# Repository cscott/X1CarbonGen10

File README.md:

# Input Module for Thinkpad X1 Carbon Gen 10 keyboard

This module is based on the "Microcontroller Input Module" example
from https://github.com/FrameworkComputer/InputModules which in turn
is based on the Adafruit Feather RP2040 (https://www.adafruit.com/product/4884).

More discussion of this project, and of replacement keyboards for
the Framework 16 laptop generally, can be found in the [Framework
forums](https://community.frame.work/t/thinkpad-keyboard-mod-super-early-stages/38484/58).

## License
Input Modules © 2023 by Framework Computer Inc is licensed under CC BY 4.0.

This module for the Thinkpad X1 Carbon Gen 10 keyboard is © 2024 by
C. Scott Ananian and is also licensed under CC BY 4.0.

To view a copy of this license,
visit http://creativecommons.org/licenses/by/4.0/

## Fabrication and Assembly
A 0.8mm PCB is recommended.

All components are SMT on the bottom side of the board.

To enter boot mode on the RP2040 to reflash, hold down the "Fn" key on
the keyboard as power is applied.

## BOM
You can find alternatives for just about each of these components
except for the microcontroller.  The keyboard FPC is designed to be inserted
with contacts facing down toward the PCB, which is "up" (since the connector
is on the bottom side of the board) and thus will require folding the
keyboard's FPC cable to achieve the proper orientation.

Notes: 1uF caps are 2.2uF in pico reference design and it had one more 100nF cap on 1v1;
match crystal caps to crystal selected.

| Item # | Designator                                         | Qty | Manufacturer                        | Mfg Part #               | Description / Value | Package/Footprint                                    | Type |
|--------|----------------------------------------------------|-----|-------------------------------------|--------------------------|---------------------|------------------------------------------------------|------|
| 1      | C1, C4, C6, C9, C11, C12, C13, C14, C15, C16, C17, C18, C20 | 13  | Samsung                    | CL05B104KO5NNNC          | 100nF               | Capacitor_SMD:C_0402_1005Metric                      | SMT  |
| 2      | C2, C3                                             | 2   | Murata                              | GRM1555C1H150JA01D       | 15pF                | Capacitor_SMD:C_0402_1005Metric                      | SMT  |
| 3      | C5, C8, C19, C21, C22, C23                         | 6   | TDK                                 | C1608X5R1A106M080AC      | 10uF                | Capacitor_SMD:C_0603_1608Metric                      | SMT  |
| 4      | C7, C10                                            | 2   | Samsung                             | CL05A105KO5NNNC          | 1uF                 | Capacitor_SMD:C_0402_1005Metric                      | SMT  |
| 5      | D1, D2, D3, D4, D5                                 | 5   | Littelfuse                          | SP0402B-ULC-01ETG        | D_TVS               | Diode_SMD:D_0402_1005Metric                          | SMT  |
| 6      | H1, H2                                             | 2   | Keystone                            | 24929                    | 24929               | InputModule:MountingHole_3.7mm_Pad_24929             | SMT  |
| 7      | J2                                                 | 1   | HDGC                                | 0.3K-HX-45PWB            | 45-pin FPC connector | 20655-045E-01:0.3K-HX-45PWB                         | SMT  |
| 8      | R1, R3                                             | 2   | Yageo                               | RC0402FR-071KL           | 1k                  | Resistor_SMD:R_0402_1005Metric                       | SMT  |
| 9      | R2                                                 | 1   | Yageo                               | RC0402FR-07330KL         | 330k                | Resistor_SMD:R_0402_1005Metric                       | SMT  |
| 10     | R4, R5                                             | 2   | Panasonic                           | ERJ-2RKF27R0X            | 27                  | Resistor_SMD:R_0402_1005Metric                       | SMT  |
| 11     | R6, R7, R8, R9                                     | 4   | Panasonic                           | ERJ-2RKF1000X            | 100                 | Resistor_SMD:R_0402_1005Metric                       | SMT  |
| 12     | U1                                                 | 1   | Winbond                             | W25Q16JVUXIQ             | W25Q16JVUXIQ        | InputModule:SON-8-1EP_3x2mm_P0.5mm_EP0.2x1.6mm       | SMT  |
| 13     | U2                                                 | 1   | Raspberry Pi                        | RP2040TR7                | RP2040              | Package_DFN_QFN:QFN-56-1EP_7x7mm_P0.4mm_EP3.2x3.2mm  | SMT  |
| 14     | U3                                                 | 1   | Microchip                           | MCP23S17_ML              | MCP23S17_ML         | Package_DFN_QFN:QFN-28-1EP_6x6mm_P0.65mm_EP4.25x4.25mm | SMT|
| 15     | Y1                                                 | 1   | Abracon                             | ABM8G-12.000MHZ-18-D2Y-T | 12.000MHz           | Crystal:Crystal_SMD_3225-4Pin_3.2x2.5mm              | SMT  |

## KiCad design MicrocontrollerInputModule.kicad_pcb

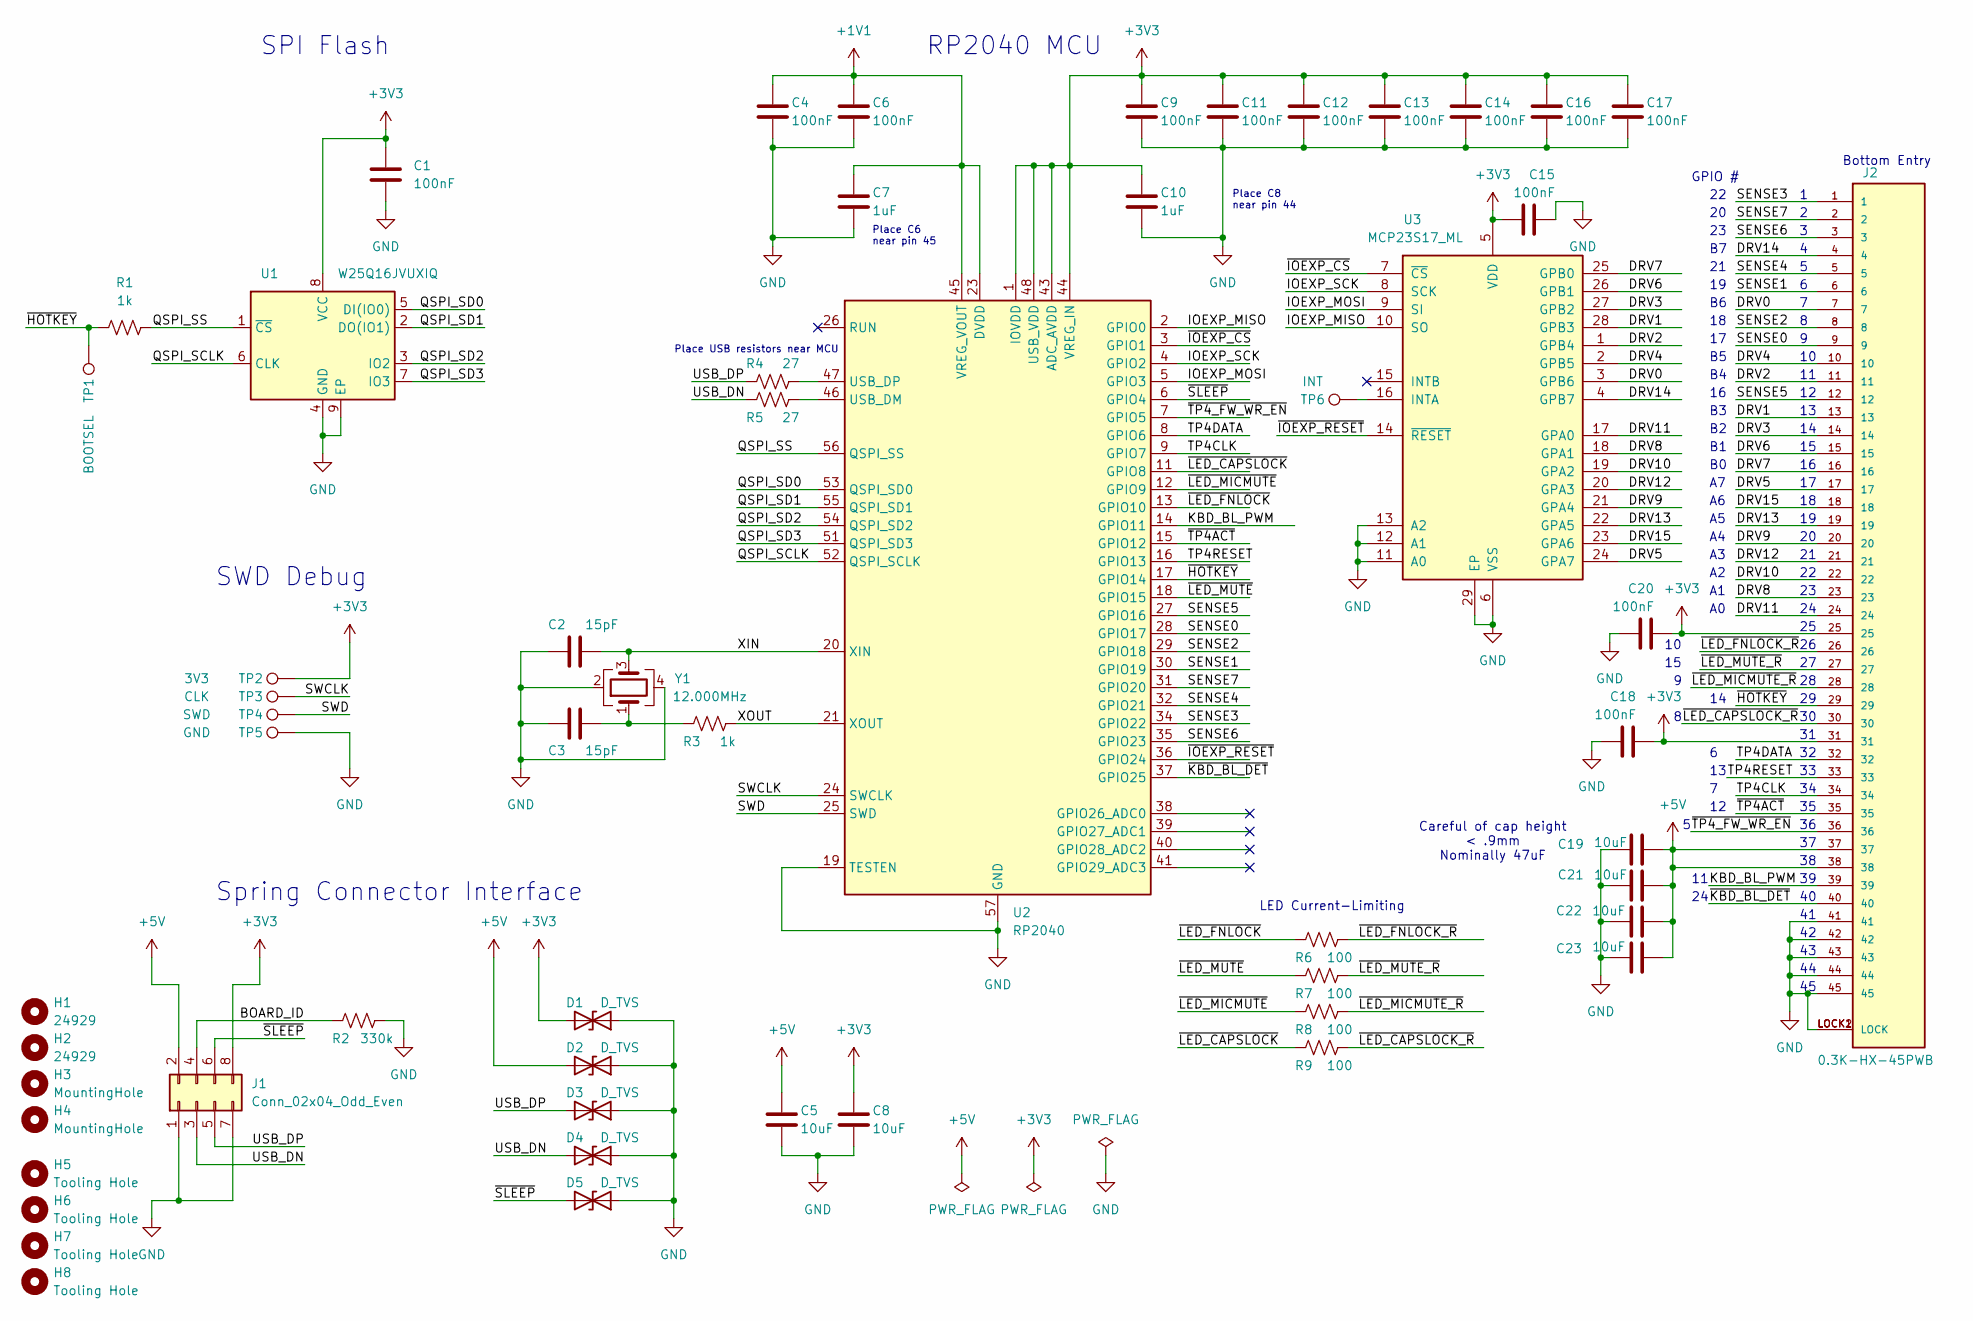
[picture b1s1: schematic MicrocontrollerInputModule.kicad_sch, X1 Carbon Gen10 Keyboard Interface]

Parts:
C1, C4, C6, C9, C11, C12, C13, C14, C15, C16, C17, C18, C20: 100nF; C_0402_1005Metric; LCSC C1525
C2, C3: 15pF; C_0402_1005Metric; LCSC C1555
C5, C8, C19, C21, C22, C23: 10uF; C_0603_1608Metric; LCSC C96446
C7, C10: 1uF; C_0402_1005Metric; LCSC C52923
D1, D2, D3, D4, D5: D_TVS; D_0402_1005Metric; LCSC C468904
H1, H2: 24929; MountingHole_3.7mm_Pad_24929; LCSC C5354888
H3, H4: MountingHole; MountingHole_2.1mm
H5, H6, H7, H8: Tooling Hole; JLCPCB Tooling Hole
J1: Conn_02x04_Odd_Even; PogoPads_2x4_P2.0mm
J2: 0.3K-HX-45PWB; PARTREV 5
R1, R3: 1k; R_0402_1005Metric; LCSC C11702
R2: 330k; R_0603_1608Metric; LCSC C23137
R4, R5: 27; R_0402_1005Metric; LCSC C138021
R6, R7, R8, R9: 100; R_0402_1005Metric; LCSC C25076
TP1: BOOTSEL; TestPoint_Pad_D1.0mm
TP2: 3V3; TestPoint_Pad_D1.0mm
TP3: CLK; TestPoint_Pad_D1.0mm
TP4: SWD; TestPoint_Pad_D1.0mm
TP5: GND; TestPoint_Pad_D1.0mm
TP6: INT; TestPoint_Pad_D1.0mm
U1: W25Q16JVUXIQ; SON-8-1EP_3x2mm_P0.5mm_EP0.2x1.6mm; LCSC C2843335
U2: RP2040; QFN-56-1EP_7x7mm_P0.4mm_EP3.2x3.2mm; LCSC C2040
U3: MCP23S17_ML; QFN-28-1EP_6x6mm_P0.65mm_EP4.25x4.25mm; LCSC C629442
Y1: 12.000MHz; Crystal_SMD_3225-4Pin_3.2x2.5mm; LCSC C9002

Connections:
+1V1: C4.1, C6.1, C7.1, U2.23 (DVDD), U2.45 (VREG_VOUT), U2.50 (DVDD)
+3V3: C1.1, C8.1, C9.1, C10.1, C11.1, C12.1, C13.1, C14.1, C15.1, C16.1, C17.1, C18.2, C20.2, D1.2 (A2), J1.8, J2.25, J2.31, TP2.1, U1.8 (VCC), U2.1 (IOVDD), U2.10 (IOVDD), U2.22 (IOVDD), U2.33 (IOVDD), U2.42 (IOVDD), U2.43 (ADC_AVDD), U2.44 (VREG_IN), U2.48 (USB_VDD), U2.49 (IOVDD), U3.5 (VDD)
+5V: C5.1, C19.2, C21.2, C22.2, C23.2, D2.2 (A2), J1.2, J2.37, J2.38
/BOARD_ID: J1.4, R2.1
/DRV0: J2.7, U3.3 (GPB6)
/DRV1: J2.13, U3.28 (GPB3)
/DRV2: J2.11, U3.1 (GPB4)
/DRV3: J2.14, U3.27 (GPB2)
/DRV4: J2.10, U3.2 (GPB5)
/DRV5: J2.17, U3.24 (GPA7)
/DRV6: J2.15, U3.26 (GPB1)
/DRV7: J2.16, U3.25 (GPB0)
/DRV8: J2.23, U3.18 (GPA1)
/DRV9: J2.20, U3.21 (GPA4)
/DRV10: J2.22, U3.19 (GPA2)
/DRV11: J2.24, U3.17 (GPA0)
/DRV12: J2.21, U3.20 (GPA3)
/DRV13: J2.19, U3.22 (GPA5)
/DRV14: J2.4, U3.4 (GPB7)
/DRV15: J2.18, U3.23 (GPA6)
/IOEXP_MISO: U2.2 (GPIO0), U3.10 (SO)
/IOEXP_MOSI: U2.5 (GPIO3), U3.9 (SI)
/IOEXP_SCK: U2.4 (GPIO2), U3.8 (SCK)
/KBD_BL_PWM: J2.39, U2.14 (GPIO11)
/QSPI_SCLK: U1.6 (CLK), U2.52 (QSPI_SCLK)
/QSPI_SD0: U1.5 (DI(IO0)), U2.53 (QSPI_SD0)
/QSPI_SD1: U1.2 (DO(IO1)), U2.55 (QSPI_SD1)
/QSPI_SD2: U1.3 (IO2), U2.54 (QSPI_SD2)
/QSPI_SD3: U1.7 (IO3), U2.51 (QSPI_SD3)
/QSPI_SS: R1.2, U1.1 (~CS), U2.56 (QSPI_SS)
/SENSE0: J2.9, U2.28 (GPIO17)
/SENSE1: J2.6, U2.30 (GPIO19)
/SENSE2: J2.8, U2.29 (GPIO18)
/SENSE3: J2.1, U2.34 (GPIO22)
/SENSE4: J2.5, U2.32 (GPIO21)
/SENSE5: J2.12, U2.27 (GPIO16)
/SENSE6: J2.3, U2.35 (GPIO23)
/SENSE7: J2.2, U2.31 (GPIO20)
/SWCLK: TP3.1, U2.24 (SWCLK)
/SWD: TP4.1, U2.25 (SWD)
/TP4CLK: J2.34, U2.9 (GPIO7)
/TP4DATA: J2.32, U2.8 (GPIO6)
/TP4RESET: J2.33, U2.16 (GPIO13)
/USB_DN: D4.2 (A2), J1.3, R5.1
/USB_DP: D3.2 (A2), J1.5, R4.1
/XIN: C2.2, U2.20 (XIN), Y1.3
/XOUT: R3.2, U2.21 (XOUT)
/~HOTKEY: J2.29, R1.1, TP1.1, U2.17 (GPIO14)
/~IOEXP_CS: U2.3 (GPIO1), U3.7 (~CS)
/~IOEXP_RESET: U2.36 (GPIO24), U3.14 (~RESET)
/~KBD_BL_DET: J2.40, U2.37 (GPIO25)
/~LED_CAPSLOCK_R: J2.30, R9.2
/~LED_CAPSLOCK: R9.1, U2.11 (GPIO8)
/~LED_FNLOCK_R: J2.26, R6.2
/~LED_FNLOCK: R6.1, U2.13 (GPIO10)
/~LED_MICMUTE_R: J2.28, R8.2
/~LED_MICMUTE: R8.1, U2.12 (GPIO9)
/~LED_MUTE_R: J2.27, R7.2
/~LED_MUTE: R7.1, U2.18 (GPIO15)
/~SLEEP: D5.2 (A2), J1.6, U2.6 (GPIO4)
/~TP4ACT: J2.35, U2.15 (GPIO12)
/~TP4_FW_WR_EN: J2.36, U2.7 (GPIO5)
GND: C1.2, C2.1, C3.1, C4.2, C5.2, C6.2, C7.2, C8.2, C9.2, C10.2, C11.2, C12.2, C13.2, C14.2, C15.2, C16.2, C17.2, C18.1, C19.1, C20.1, C21.1, C22.1, C23.1, D1.1 (A1), D2.1 (A1), D3.1 (A1), D4.1 (A1), D5.1 (A1), J1.1, J1.7, J2.41, J2.42, J2.43, J2.44, J2.45, J2.LOCK1 (LOCK), J2.LOCK2 (LOCK), R2.2, TP5.1, U1.4 (GND), U1.9 (EP), U2.19 (TESTEN), U2.57 (GND), U3.6 (VSS), U3.11 (A0), U3.12 (A1), U3.13 (A2), U3.29 (EP), Y1.2, Y1.4
unnamed: C3.2, R3.1, Y1.1
unnamed: R5.2, U2.46 (USB_DM)
unnamed: R4.2, U2.47 (USB_DP)
unnamed: TP6.1, U3.16 (INTA)

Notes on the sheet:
SPI Flash
Bottom Entry
LED Current-Limiting
Place C8 near pin 44
GPIO #
Place USB resistors near MCU
Spring Connector Interface
Place C6 near pin 45
RP2040 MCU
Careful of cap height < .9mm Nominally 47uF
SWD Debug

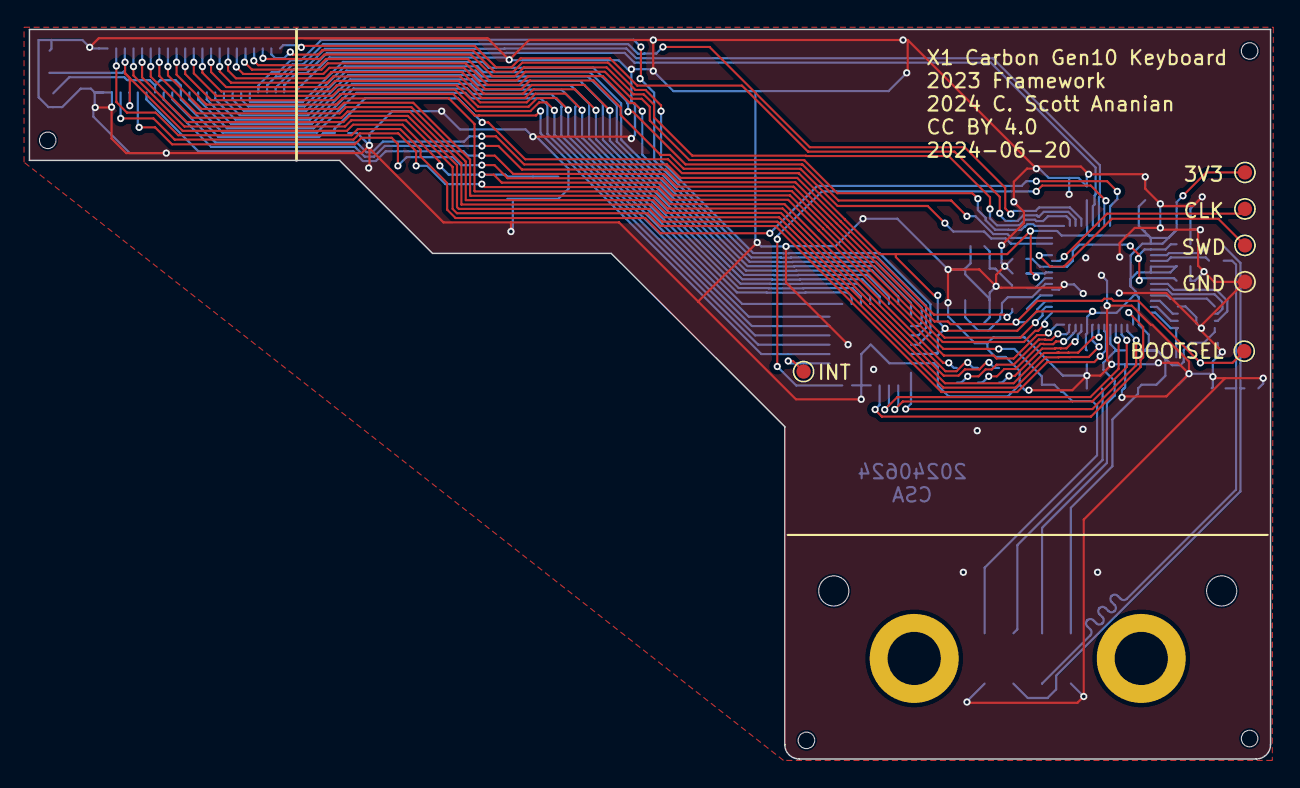
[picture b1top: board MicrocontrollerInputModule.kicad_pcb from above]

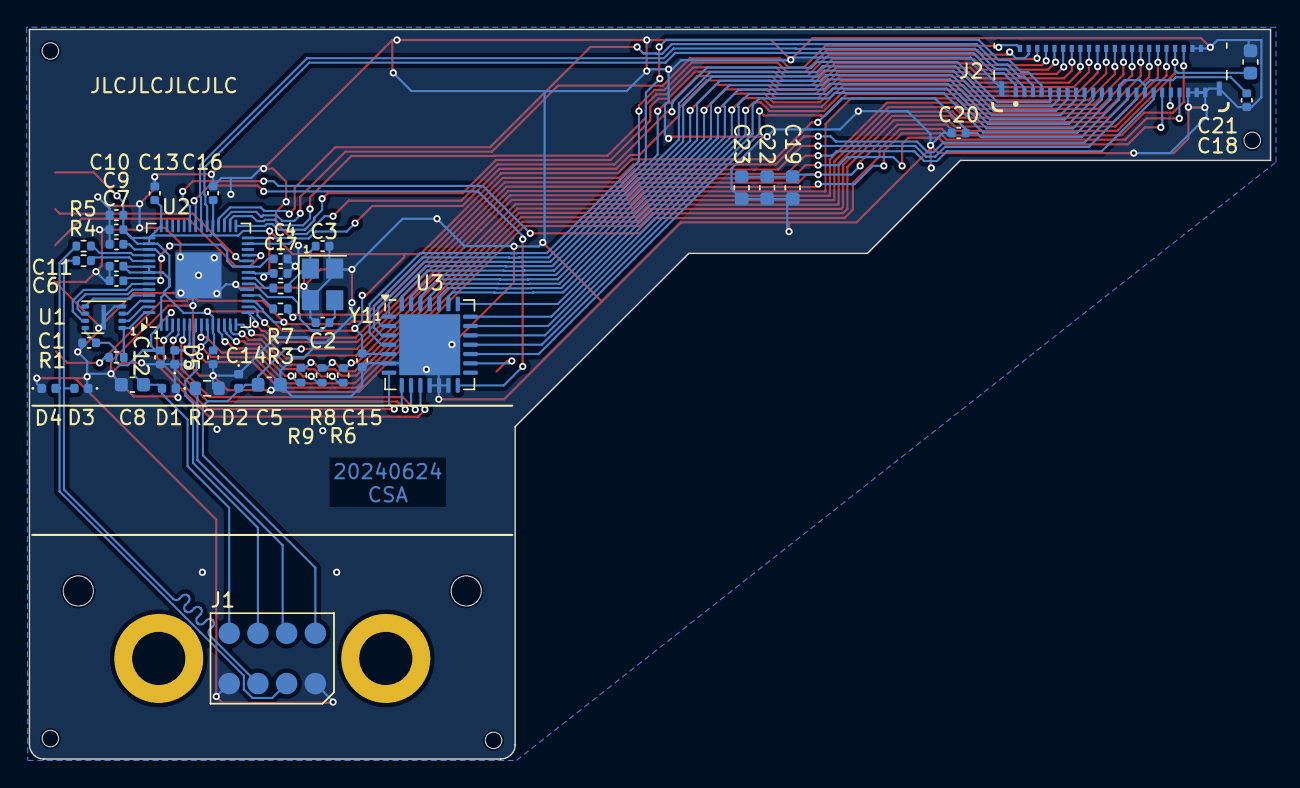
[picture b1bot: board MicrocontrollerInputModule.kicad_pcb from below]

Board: 2 copper layers, 86.4 x 50.8 mm, 57 parts (45 on the bottom side), 67 nets.

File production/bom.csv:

Designator,Footprint,Quantity,Value,LCSC Part #
"C1, C11, C12, C13, C14, C15, C16, C17, C18, C20, C4, C6, C9",0402,13,100nF,C1525
"C10, C7",0402,2,1uF,C52923
"C19, C21, C22, C23, C5, C8",0603,6,10uF,C96446
"C2, C3",0402,2,15pF,C1555
"D1, D2, D3, D4, D5",0402,5,D_TVS,C468904
J2,0.3K-HX-45PWB,1,0.3K-HX-45PWB,
"R1, R3",0402,2,1k,C11702
R2,0603,1,330k,C23137
"R4, R5",0402,2,27,C138021
"R6, R7, R8, R9",0402,4,100,C25076
U1,SON-8-1EP_3x2mm_P0.5mm_EP0.2x1.6mm,1,W25Q16JVUXIQ ,C2843335
U2,QFN-56-1EP_7x7mm_P0.4mm_EP3.2x3.2mm,1,RP2040,C2040
U3,QFN-28-1EP_6x6mm_P0.65mm_EP4.25x4.25mm,1,MCP23S17_ML,C629442
Y1,Crystal_SMD_3225-4Pin_3.2x2.5mm,1,12.000MHz,C9002

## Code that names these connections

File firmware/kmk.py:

print("Starting")

import microcontroller
import board
import digitalio
import busio
import time
from adafruit_mcp230xx.mcp23017 import MCP23017

from keypad import Event as KeyEvent
from kmk.kmk_keyboard import KMKKeyboard
from kmk.scanners import Scanner
from kmk.scanners.keypad import KeysScanner
from kmk.keys import KC
from kmk.extensions.lock_status import LockStatus

i2c = busio.I2C(microcontroller.pin.GPIO1, microcontroller.pin.GPIO0)
ioexp_reset = digitalio.DigitalInOut(microcontroller.pin.GPIO2)
ioexp_reset.switch_to_output(False)
time.sleep(0.05)
ioexp_reset.switch_to_output(True)
time.sleep(0.05)
mcp = MCP23017(i2c)

class MyScanner(Scanner):
    def __init__(self):
        self.drv = [None] * 16
        for ionum, p in enumerate([
                11, 8, 10, 12, 9, 13, 15, 5,
                7, 6, 3, 1, 2, 4, 0, 14
        ]):
            self.drv[p] = mcp.get_pin(ionum)
            self.drv[p].switch_to_input(pull=digitalio.Pull.UP)
        self.sense = [None] * 8
        for ionum, p in enumerate([ 5, 0, 2, 1, 7, 4, 3, 6 ]):
            pin = getattr(microcontroller.pin, 'GPIO' + str(16 + ionum))
            self.sense[p] = digitalio.DigitalInOut(pin)
            self.sense[p].switch_to_input(pull=digitalio.Pull.UP)
        self.len_rows = len(self.drv)
        self.len_cols = len(self.sense)
        self._key_count = self.len_rows * self.len_cols
        initial_state_value = b'\x01'
        self.state = bytearray(initial_state_value) * self._key_count
        self.offset = 0

    @property
    def key_count(self):
        return self._key_count

    def scan_for_changes(self):
        '''
        Poll the matrix for changes and return either None (if nothing updated)
        or a bytearray (reused in later runs so copy this if you need the raw
        array itself for some crazy reason) consisting of (row, col, pressed)
        which are (int, int, bool)
        '''
        ba_idx = 0
        any_changed = False

        for oidx, opin in enumerate(self.drv):
            opin.switch_to_output(False)

            for iidx, ipin in enumerate(self.sense):
                # cast to int to avoid
                #
                # >>> xyz = bytearray(3)
                # >>> xyz[2] = True
                # Traceback (most recent call last):
                #   File "<stdin>", line 1, in <module>
                # OverflowError: value would overflow a 1 byte buffer
                #
                # I haven't dived too far into what causes this, but it's
                # almost certainly because bool types in Python aren't just
                # aliases to int values, but are proper pseudo-types
                new_val = int(ipin.value)
                old_val = self.state[ba_idx]

                if old_val != new_val:
                    row = oidx
                    col = iidx

                    pressed = not new_val # active low
                    self.state[ba_idx] = new_val

                    any_changed = True
                    break

                ba_idx += 1

            opin.switch_to_input(pull=digitalio.Pull.UP)
            if any_changed:
                break

        if any_changed:
            key_number = self.len_cols * row + col + self.offset
            return KeyEvent(key_number, pressed)

class MyKeyboard(KMKKeyboard):
    def __init__(self):
        self.matrix = [
            MyScanner(),
            KeysScanner(
                pins=[ microcontroller.pin.GPIO14 ], # HOTKEY
                value_when_pressed = False,
                pull = True
            )
        ]
        self.keymap = [
            [
                # DRV0
                KC.GRAVE, KC.N1, KC.Q, KC.TAB, KC.A, KC.ESCAPE, KC.Z, KC.NO,
                # DRV1
                KC.F1, KC.N2, KC.W, KC.CAPSLOCK, KC.S, KC.NO, KC.X, KC.NO,
                # DRV2
                KC.F2, KC.N3, KC.E, KC.F3, KC.D, KC.F4, KC.C, KC.NO,
                # DRV3
                KC.N5, KC.N4, KC.R, KC.T, KC.F, KC.G, KC.V, KC.B,
                # DRV4
                KC.N6, KC.N7, KC.U, KC.Y, KC.J, KC.H, KC.M, KC.N,
                # DRV5
                KC.EQUAL, KC.N8, KC.I, KC.RBRACKET, KC.K, KC.F6, KC.COMMA, KC.NO,
                # DRV6
                KC.F8, KC.N9, KC.O, KC.F7, KC.L, KC.NO, KC.DOT, KC.NO,
                # DRV7
                KC.MINUS, KC.N0, KC.P, KC.LBRACKET, KC.SCOLON, KC.QUOTE, KC.NO, KC.SLASH,
                # DRV8
                KC.F9, KC.F10, KC.NO, KC.BSPACE, KC.BSLASH, KC.F5, KC.ENTER, KC.SPACE,
                # DRV9
                KC.INSERT, KC.F12, KC.NO, KC.LGUI, KC.NO, KC.NO, KC.NO, KC.RIGHT,
                # DRV10
                KC.DELETE, KC.F11, KC.NO, KC.NO, KC.NO, KC.NO, KC.NO, KC.DOWN,
                # DRV11
                KC.PGUP, KC.PGDOWN, KC.NO, KC.NO, KC.NO, KC.NO, KC.NO, KC.NO,
                # DRV12
                KC.HOME, KC.END, KC.NO, KC.NO, KC.NO, KC.UP, KC.NO, KC.LEFT,
                # DRV13
                KC.NO, KC.PSCREEN, KC.NO, KC.NO, KC.NO, KC.LALT, KC.NO, KC.RALT,
                # DRV14
                KC.NO, KC.NO, KC.NO, KC.LSHIFT, KC.NO, KC.NO, KC.RSHIFT, KC.NO,
                # DRV15
                KC.LCTRL, KC.NO, KC.NO, KC.NO, KC.NO, KC.NO, KC.RCTRL, KC.NO
            ],
        ]

capslock = digitalio.DigitalInOut(microcontroller.pin.GPIO8)
capslock.switch_to_output(True)
class LEDLockStatus(LockStatus):
    def set_lock_leds(self):
        capslock.value = not self.get_caps_lock()
    def after_hid_send(self, sandbox):
        super().after_hid_send(sandbox)  # Critically important. Do not forget
        if self.report_updated:
            self.set_lock_leds()

keyboard = MyKeyboard()
keyboard.extensions.append(LEDLockStatus())

if __name__ == '__main__':
    keyboard.go()

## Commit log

2023-03-12 Rename to Microcontroller Input Module
2023-03-12 Rename again.
2023-03-12 Fix some footprints
2023-03-12 Minimal Small Input Module
2024-01-24 Re-add .gitignore file from InputModules parent
2024-01-25 Initial reconfiguration for X1 Carbon Gen10 Keyboard module
    RP2040 pin assignments are somewhat arbitrary; PCB is not yet routed;
    position of framework input module connector is also arbitrary.
2024-01-26 First complete version, fully routed
2024-01-26 Renumber components, tidy up silkscreen
2024-01-26 Update README; change C19 to an 0603 cap; improve ground plane connectivity
2024-01-28 Add some basic firmware for this keyboard, implemented in CircuitPython
2024-01-28 Improvements to the firmware
2024-01-28 Swap TP4CLK and TP4DATA to handle PIO requirements
    The current RP2040 PS/2 driver in:
    https://github.com/qmk/qmk_firmware/blob/master/platforms/chibios/drivers/vendor/RP/RP2040/ps2_vendor.c#L24
    requires that PS2_DATA_PIN is the one *before* PS2_CLOCK_PIN, so swap our
    GPIO assignments to match.
2024-01-29 Switch to 23S17 from 23017
    This increases the scan rate by ~5x (from 1.7MHz clock to 10MHz) and also
    works around an erratum (?) in the 23017 which forces the A7 and B7 gpios
    to be outputs. This could lead to a short circuit if (for example)
    a key on the same SENSE line is held down in both the A7 and some other
    row -- A7 would be driven high (because it can't be three-stated) while
    the other row is driven low, and a direct connection exists through
2024-01-29 Update with BOM information
2024-01-29 Add footprint for an alternative FPC connector (stocked by JLCPCB)
    We're not going to switch our design to use this yet, but it's here for
    future use.
2024-01-29 Version sent to JLCPCB for assembly 2024-01-29
2024-01-31 Update renderings of the board
2024-01-31 Create FUNDING.yml
    Accept funding to underwrite purchase of candidate thinkpad keyboards
2024-02-02 README: add link to forum discussion
2024-06-19 Last kicad v7 version
2024-06-20 kicad v8
2024-06-20 Size test for relocating the FPC connector
2024-06-21 Update to use new FPC connector and position, fix sense resistor, etc
2024-06-21 Second version sent to JLCPCB
2024-06-29 Documentation and 3d model updates
2024-06-30 Update 3d models
2024-06-30 Adjust board thickness to 0.8mm

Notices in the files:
MicrocontrollerInputModule.kicad_pcb:
This work is licensed under a Creative Commons Attribution 4.0 International License
